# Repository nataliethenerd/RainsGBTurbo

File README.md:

# GameBoy Color Turbo 

https://github.com/user-attachments/assets/9c1e9254-65e6-4811-b10f-9467ac8f224d

aka Rain's Turbo (made for Rain)

This flex PCB is made for a GBC PCB to add a turbo button mode to the B button. You could rework the PCB to make it work on any other button. This one was made with Metroid II in mind.

You can support me on Ko-Fi

**My socials**

• [Twitter](https://twitter.com/natalie_thenerd) 

• [Instagram](https://www.instagram.com/natalie.thenerd/) 

• [Modded Gameboy Club](https://moddedgameboy.club/) - a club dedicated to the modification of Game Boys, freely sharing resources

## Building the PCB

Order from your favourite fab as a flex PCB. 

### BOM
| Designator | Part | Link |
|-------------| -----| -----|
| U1 | CH552E | [AliExpress Link](https://s.click.aliexpress.com/e/_DBPrq0r)
| R1 | 0603 1K |
| C1, C2 | 0603 100nF |
| Program Button | x | [AliExpress Link](https://s.click.aliexpress.com/e/_DCfsiNZ)
| Trigger Button | 7mm if you want to cut the shell, 5-6mm otherwise | [AliExpress Link](https://s.click.aliexpress.com/e/_DlA5P0j)

## Programing

Solder up a USB to the 5V, GND, D+ and D- pads. To set up with Arduino, please follow the instructions here

https://github.com/DeqingSun/ch55xduino

## License

Please do not remove my logo, website and name.

The CC BY-SA 4.0 (Creative Commons Attribution-ShareAlike 4.0 International) license allows you to:

1. **Share** - Copy and redistribute the material in any medium or format.
2. **Adapt** - Remix, transform, and build upon the material for any purpose, even commercially.

### Conditions:

- **Attribution** - You must give appropriate credit, provide a link to the license, and indicate if changes were made. You may do so in any reasonable manner, but not in any way that suggests the licensor endorses you or your use.
- **ShareAlike** - If you remix, transform, or build upon the material, you must distribute your contributions under the same license as the original.

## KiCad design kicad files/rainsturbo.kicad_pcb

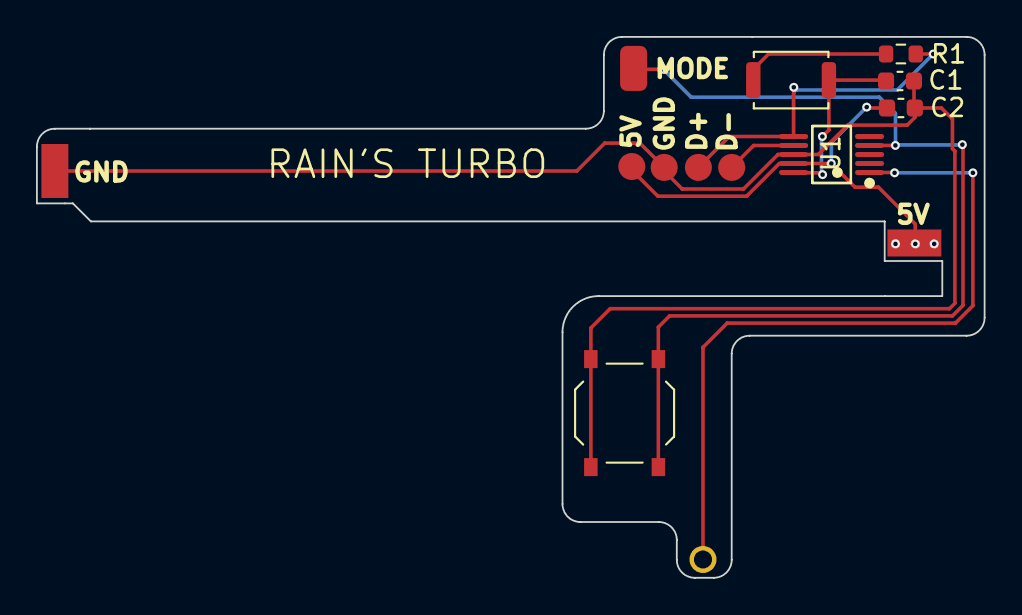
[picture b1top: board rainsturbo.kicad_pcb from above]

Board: 2 copper layers, 52.7 x 30.0 mm, 7 parts (0 on the bottom side), 7 nets.

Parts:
C1, C2: 100nF; C_0603_1608Metric
J1: B; TestPoint_Loop_D1.80mm_Drill1.0mm_Beaded
R1: 1K; R_0603_1608Metric
SW1: SW_Push; SW_Push_1P1T_XKB_TS-1187A
SW2: SW_Push; SW_Push_SPST_NO_Alps_SKRK
U1: MSOP-10_L3.0-W3.0-P0.50-LS5.0-BL

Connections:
+5V: C2.1, U1.9 (VCC)
/D+: R1.1, U1.6 (P3.6)
GND: C1.2, C2.2, SW1.1, U1.8 (GND)
unnamed: J1.1, U1.1 (P1.4)
unnamed: R1.2, SW2.1
unnamed: SW1.2, U1.4 (P1.7)
unnamed: C1.1, SW2.2, U1.10 (V33)

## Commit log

2024-07-20 kicad
